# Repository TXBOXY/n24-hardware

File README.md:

# TXBoxy-n24 Hardware

This repository contains the hardware design files for the TXBoxy-n24(-LR). The PCB is designed using KiCad.

# License
<br />This work is licensed under a <a rel="license" href="http://creativecommons.org/licenses/by-sa/4.0/">Creative Commons Attribution-ShareAlike 4.0 International License</a>.
Other licenses may apply to the files in sub-folders.

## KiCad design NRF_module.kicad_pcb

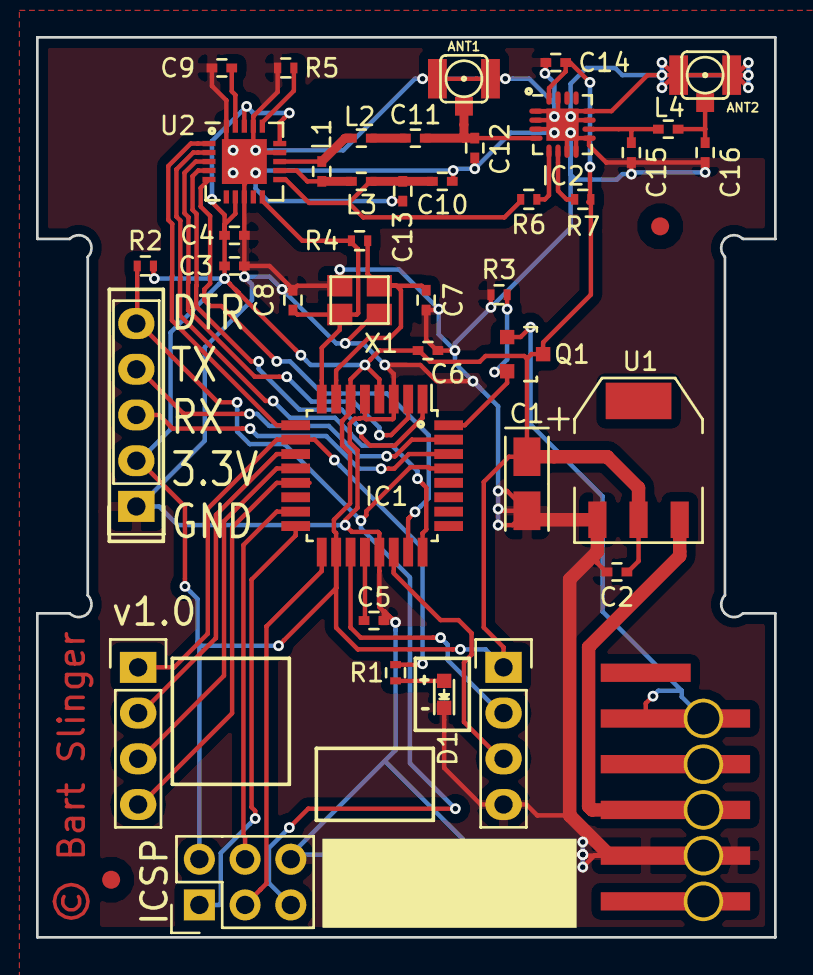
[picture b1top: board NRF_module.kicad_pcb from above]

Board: 2 copper layers, 41.0 x 50.0 mm, 41 parts (0 on the bottom side), 37 nets.

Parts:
ANT1, ANT2: FILTER; coaxial_u.fl-r-smt-1
C1: 10uF; TantalC_SizeA_EIA-3216_Wave
C2, C5, C6, C14: 0.1uF; C_0402
C3: 10nF; C_0402
C4: 1nF; C_0402
C7, C8: 22pF; C_0402
C9: 33nF; C_0402
C10: 2.2nF; C_0402
C11: 1.5pF; C_0402
C12: 1.0pF; C_0402
C13: 4.7pF; C_0402
C15, C16: 2pF; C_0402
CON1: AVR-ISP-6; Pin_Header_Straight_2x03
D1: LED; LED-0603
IC1: ATMEGA168-M; TQFP-32_7x7mm_Pitch0.8mm
IC2: RXF2401c; QFN-16-1EP_3x3mm_Pitch0.5mm
L1: 8.2nH; C_0402
L2: 3.9nH; C_0402
L3: 2.7nH; C_0402
L4: 1.5nH; C_0402
P1: STACKABLE_LEFT; Pin_Header_Straight_1x04
P2: STACKABLE_RIGHT; Pin_Header_Straight_1x04
P3: 5PIN_MALE; Pin_Header_Straight_1x05
P4: CONN_01X05; PPM_Connector
Q1: BSS138; SOT-23
R1: 330R; R_0402
R2: 4.7k; R_0402
R3: 10k; R_0402
R4: 1M; R_0402
R5: 22k; R_0402
R6, R7: 1k; R_0402
U1: APE8865N-33-HF-3; SOT-223
U2: NRF24L01; QFN-20-1EP_4x4mm_Pitch0.5mm
X1: CRYSTAL_SMD; crystal_FA238-TSX3225

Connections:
/Arduino/A6: IC1.19, P2.2
/Arduino/A7: IC1.22, P2.3
/Arduino/CE: IC1.9, U2.1
/Arduino/CSN: IC1.24, U2.2
/Arduino/D6: IC1.10, P1.1, R1.1
/Arduino/D7: IC1.11, P1.2
/Arduino/D8: IC1.12, P1.3
/Arduino/D9: IC1.13, P1.4
/Arduino/DTR: CON1.5, IC1.29, P3.5, R2.2
/Arduino/H_MISO: CON1.1, IC1.16
/Arduino/H_MOSI: CON1.4, IC1.15
/Arduino/H_SCK: CON1.3, IC1.17
/Arduino/MISO: IC1.23, U2.5
/Arduino/MOSI: IC1.1, U2.4
/Arduino/PPM: IC1.32, Q1.2, R3.1
/Arduino/RX: IC1.30, P3.3
/Arduino/SCK: IC1.2, U2.3
/Arduino/TX: IC1.31, P3.4
/Arduino/XTAL1: C7.2, IC1.7, R4.1, X1.2
/NRF24L01 Radio/VDD_PA: C10.1, C13.1, L3.1, R6.2, U2.11
/NRF24L01 Radio/XC1: C8.2, IC1.8, R4.2, U2.10, X1.1
/PPM: P4.1, Q1.1
GND: ANT1.2, ANT2.2, C1.2, C2.2, C3.2, C4.2, C5.2, C6.2, C7.1, C8.1, C9.2, C10.2, C12.2, C13.2, C14.1, C15.2, C16.2, CON1.6, D1.1, IC1.3, IC1.5, IC1.21, IC2.1, IC2.2, IC2.3, IC2.7, IC2.8, IC2.9, IC2.11, IC2.12, IC2.15, IC2.17, P2.4, P3.1, P4.4, R3.2, R5.1, U1.1, U2.8, U2.14, U2.17, U2.20, U2.21, X1.3
unnamed: ANT1.1, C11.2, C12.1, IC2.4
unnamed: ANT2.1, C16.1, L4.1
unnamed: C5.1, IC1.20
unnamed: C9.1, U2.19
unnamed: C11.1, L2.2
unnamed: C15.1, IC2.10, L4.2
unnamed: D1.2, R1.2
unnamed: IC2.5, R6.1
unnamed: IC2.6, R7.1
unnamed: L1.1, L3.2, U2.12
unnamed: L1.2, L2.1, U2.13
unnamed: R5.2, U2.16
RAW: P4.3, U1.3
VCC_ARDUINO: C1.1, C2.1, C3.1, C4.1, C6.1, C14.2, CON1.2, IC1.4, IC1.6, IC1.18, IC2.16, P2.1, P3.2, Q1.3, R2.1, R7.2, U1.2, U2.7, U2.15, U2.18

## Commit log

2016-03-21 License and gitignore
2016-03-21 Add image
2016-03-21 Adding PCB design files
2016-03-21 PDF of schematics

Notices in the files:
NRF_module.kicad_pcb:
© Bart Slinger
